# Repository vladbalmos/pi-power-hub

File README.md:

# System requirements
* micropython
* ampy
* minicom (optional)

# Development
Build micropython:

    cd [mycropython-dir]
    make -C mpy-cross

    cd [mycropython-dir]/ports/rp2
    make -j4 BOARD=PICO_W submodules
    make -j4 BOARD=PICO_W clean
    make -j4 BOARD=PICO_W
    
Set wifi SSID & password:

    cp wifi_credentials.template src/wifi_credentials.py
    # edit src/wifi_credentials.py and add SSID & SSID password

Init:

    pip3 install -r requirements.txt
    ./setup.sh
    make build
    
Run:

    make run
    
Clean

    make clean
    
Upload

    make upload
    
Build

    make build

# Topics
* vb/devices/power/pihub/request
    - device subscribes for state change requests
* vb/devices/power/pihub/response
    - device publishes state changes
* vb/devices/request
    - device subscribes for registration requests
* vb/devices/response
    - device publishes device registration data

# Status LED meanings:
* red
    - board initializing
* blue
    - connecting to mqtt server
* green
    - connected to mqtt server
* yellow
    - lost connection to mqtt

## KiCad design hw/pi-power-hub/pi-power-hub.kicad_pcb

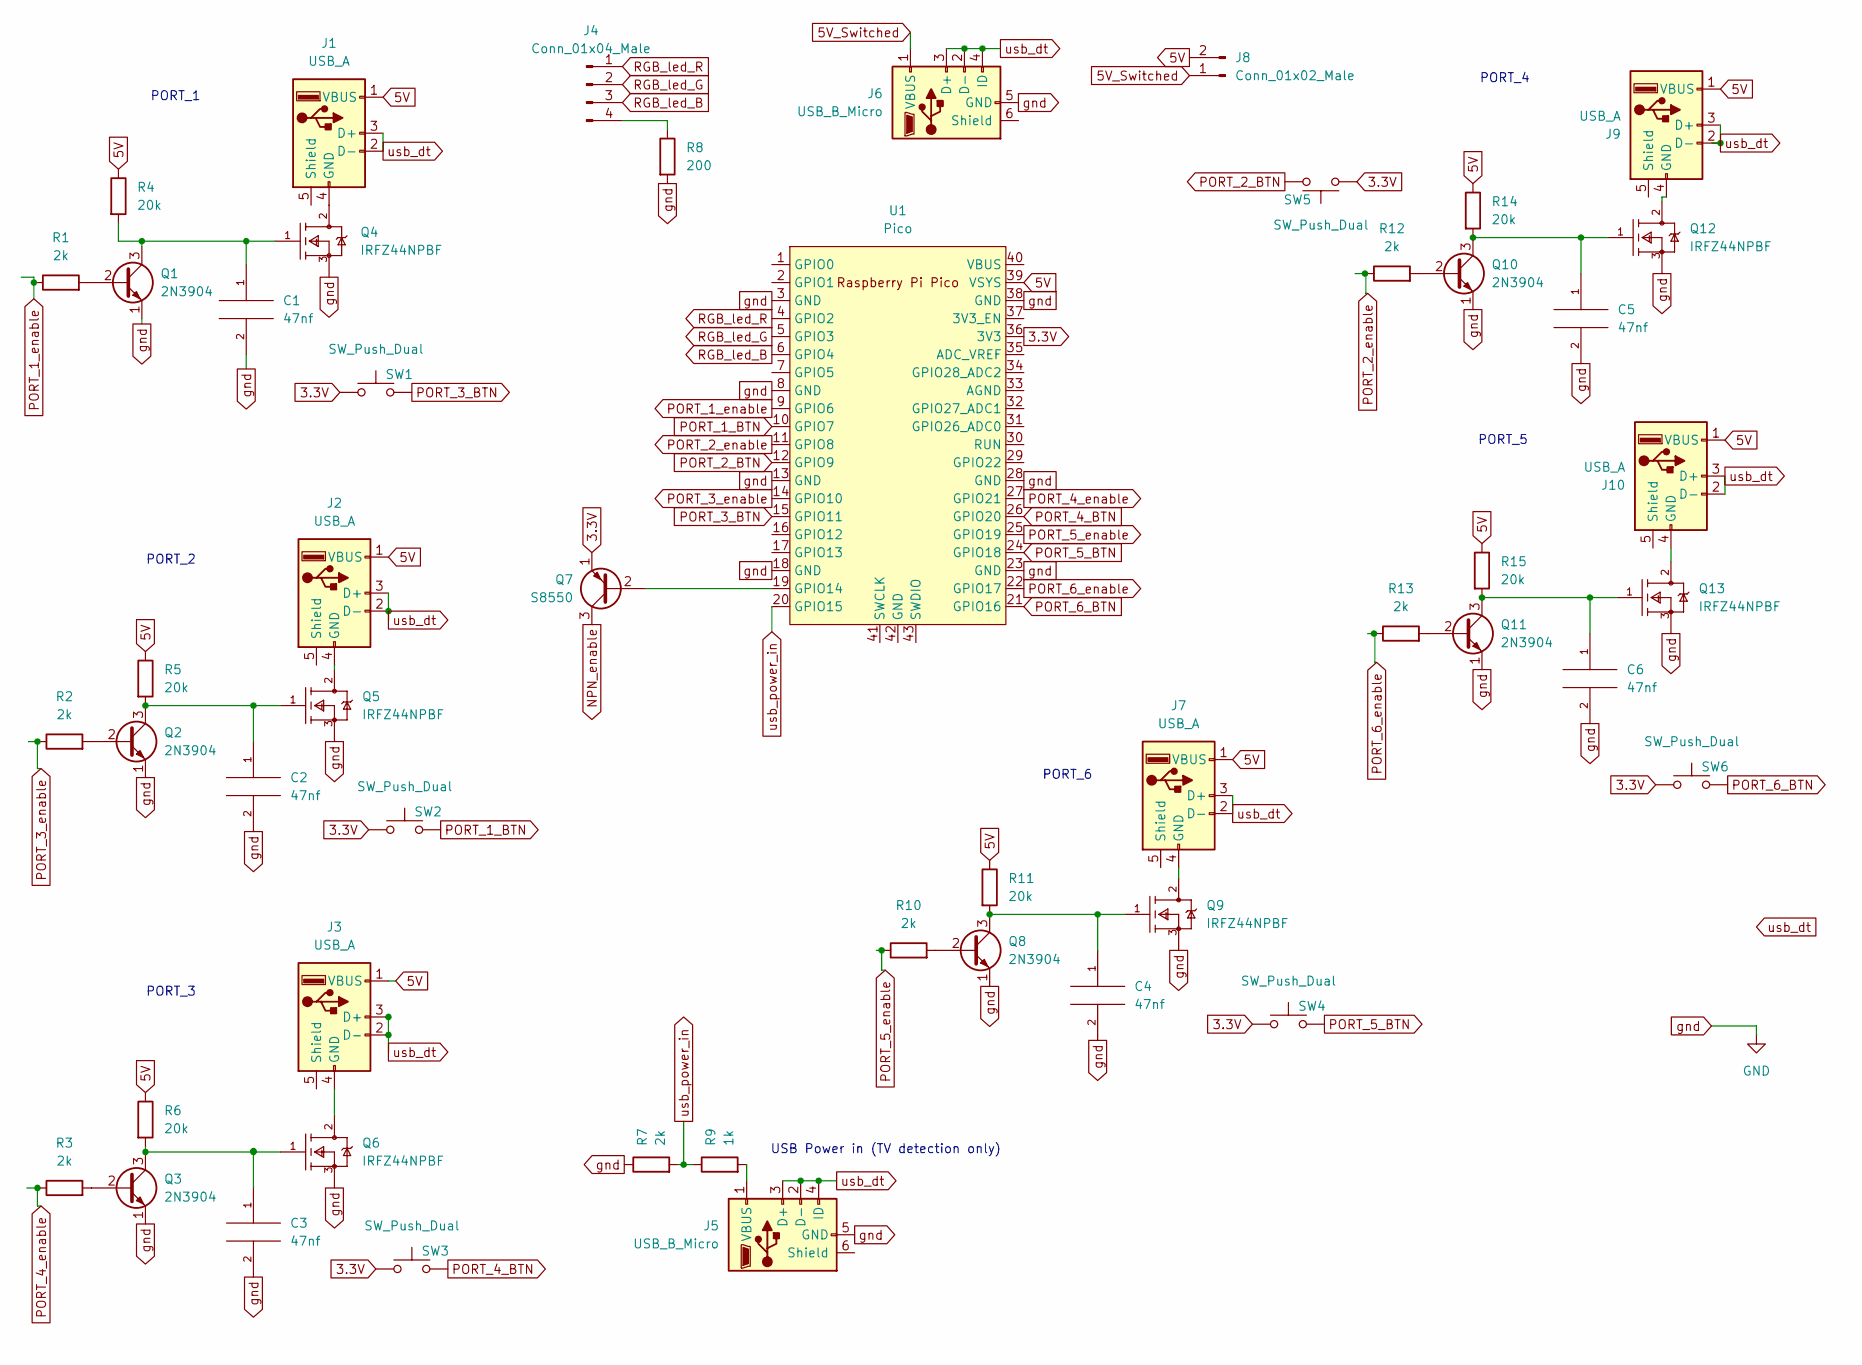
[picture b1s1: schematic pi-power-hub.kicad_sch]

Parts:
C1, C2, C3, C4, C5, C6: 47nf; C_Disc_D3.8mm_W2.6mm_P2.50mm
J1, J2, J3, J7, J9, J10: USB_A; USB_A_Molex_67643_Horizontal
J4: Conn_01x04_Male; JST_PH_B4B-PH-K_1x04_P2.00mm_Vertical
J5, J6: USB_B_Micro; USB_Micro-B_Amphenol_10103594-0001LF_Horizontal
J8: Conn_01x02_Male; JST_XH_B2B-XH-A_1x02_P2.50mm_Vertical
Q1, Q2, Q3, Q8, Q10, Q11: 2N3904; TO-92_Inline
Q4, Q5, Q6, Q9, Q12, Q13: IRFZ44NPBF; Infineon_Technologies_AG-IRFZ44NPBF-0; mouser part number 942-IRFZ44NPBF; digikey description N-Channel 55V 49A (Tc) 94W (Tc) Through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
Q7: S8550; TO-92_Inline
R1, R2, R3, R7, R10, R12, R13: 2k; R_Axial_DIN0207_L6.3mm_D2.5mm_P7.62mm_Horizontal
R4, R5, R6, R11, R14, R15: 20k; R_Axial_DIN0207_L6.3mm_D2.5mm_P7.62mm_Horizontal
R8: 200; R_Axial_DIN0207_L6.3mm_D2.5mm_P7.62mm_Horizontal
R9: 1k; R_Axial_DIN0207_L6.3mm_D2.5mm_P7.62mm_Horizontal
SW1, SW2, SW3, SW4, SW5, SW6: SW_Push_Dual; SW_PUSH_6mm_H8.5mm
U1: Pico; RPi_Pico_SMD_TH

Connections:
3.3V: Q7.1 (E), SW1.1, SW2.1, SW3.1, SW4.1, SW5.1, SW6.1, U1.36 (3V3)
5V: J1.1 (VBUS), J2.1 (VBUS), J3.1 (VBUS), J7.1 (VBUS), J8.2, J9.1 (VBUS), J10.1 (VBUS), R4.1, R5.1, R6.1, R11.1, R14.1, R15.1, U1.39 (VSYS); also elsewhere on the board
5V_Switched: J6.1 (VBUS), J8.1
NPN_enable: Q7.3 (C)
unnamed: C1.1, Q1.3 (C), Q4.1 (GATE), R4.2
unnamed: C2.1, Q2.3 (C), Q5.1 (GATE), R5.2
unnamed: C3.1, Q3.3 (C), Q6.1 (GATE), R6.2
unnamed: C4.1, Q8.3 (C), Q9.1 (GATE), R11.2
unnamed: C5.1, Q10.3 (C), Q12.1 (GATE), R14.2
unnamed: C6.1, Q11.3 (C), Q13.1 (GATE), R15.2
unnamed: J1.4 (GND), Q4.2 (DRAIN)
unnamed: J2.4 (GND), Q5.2 (DRAIN)
unnamed: J3.4 (GND), Q6.2 (DRAIN)
unnamed: J4.4, R8.1
unnamed: J5.1 (VBUS), R9.2
unnamed: J7.4 (GND), Q9.2 (DRAIN)
unnamed: J9.4 (GND), Q12.2 (DRAIN)
unnamed: J10.4 (GND), Q13.2 (DRAIN)
unnamed: Q1.2 (B), R1.2
unnamed: Q2.2 (B), R2.2
unnamed: Q3.2 (B), R3.2
unnamed: Q7.2 (B), U1.19 (GPIO14)
unnamed: Q8.2 (B), R10.2
unnamed: Q10.2 (B), R12.2
unnamed: Q11.2 (B), R13.2
PORT_1_BTN: SW2.2, U1.10 (GPIO7)
PORT_1_enable: R1.1, U1.9 (GPIO6)
PORT_2_BTN: SW5.2, U1.12 (GPIO9)
PORT_2_enable: R12.1, U1.11 (GPIO8)
PORT_3_BTN: SW1.2, U1.15 (GPIO11)
PORT_3_enable: R2.1, U1.14 (GPIO10)
PORT_4_BTN: SW3.2, U1.26 (GPIO20)
PORT_4_enable: R3.1, U1.27 (GPIO21)
PORT_5_BTN: SW4.2, U1.24 (GPIO18)
PORT_5_enable: R10.1, U1.25 (GPIO19)
PORT_6_BTN: SW6.2, U1.21 (GPIO16)
PORT_6_enable: R13.1, U1.22 (GPIO17)
RGB_led_B: J4.3, U1.6 (GPIO4)
RGB_led_G: J4.2, U1.5 (GPIO3)
RGB_led_R: J4.1, U1.4 (GPIO2)
gnd: C1.2, C2.2, C3.2, C4.2, C5.2, C6.2, J5.5 (GND), J6.5 (GND), Q1.1 (E), Q2.1 (E), Q3.1 (E), Q4.3 (SOURCE), Q5.3 (SOURCE), Q6.3 (SOURCE), Q8.1 (E), Q9.3 (SOURCE), Q10.1 (E), Q11.1 (E), Q12.3 (SOURCE), Q13.3 (SOURCE), R7.1, R8.2, U1.3 (GND), U1.8 (GND), U1.13 (GND), U1.18 (GND), U1.23 (GND), U1.28 (GND), U1.38 (GND)
usb_dt: J1.2 (D-), J1.3 (D+), J2.2 (D-), J2.3 (D+), J3.2 (D-), J3.3 (D+), J5.2 (D-), J5.3 (D+), J5.4 (ID), J6.2 (D-), J6.3 (D+), J6.4 (ID), J7.2 (D-), J7.3 (D+), J9.2 (D-), J9.3 (D+), J10.2 (D-), J10.3 (D+)
usb_power_in: R7.2, R9.1, U1.20 (GPIO15)

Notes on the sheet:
PORT_2
PORT_3
PORT_5
USB Power in (TV detection only)
PORT_4
PORT_1
PORT_6

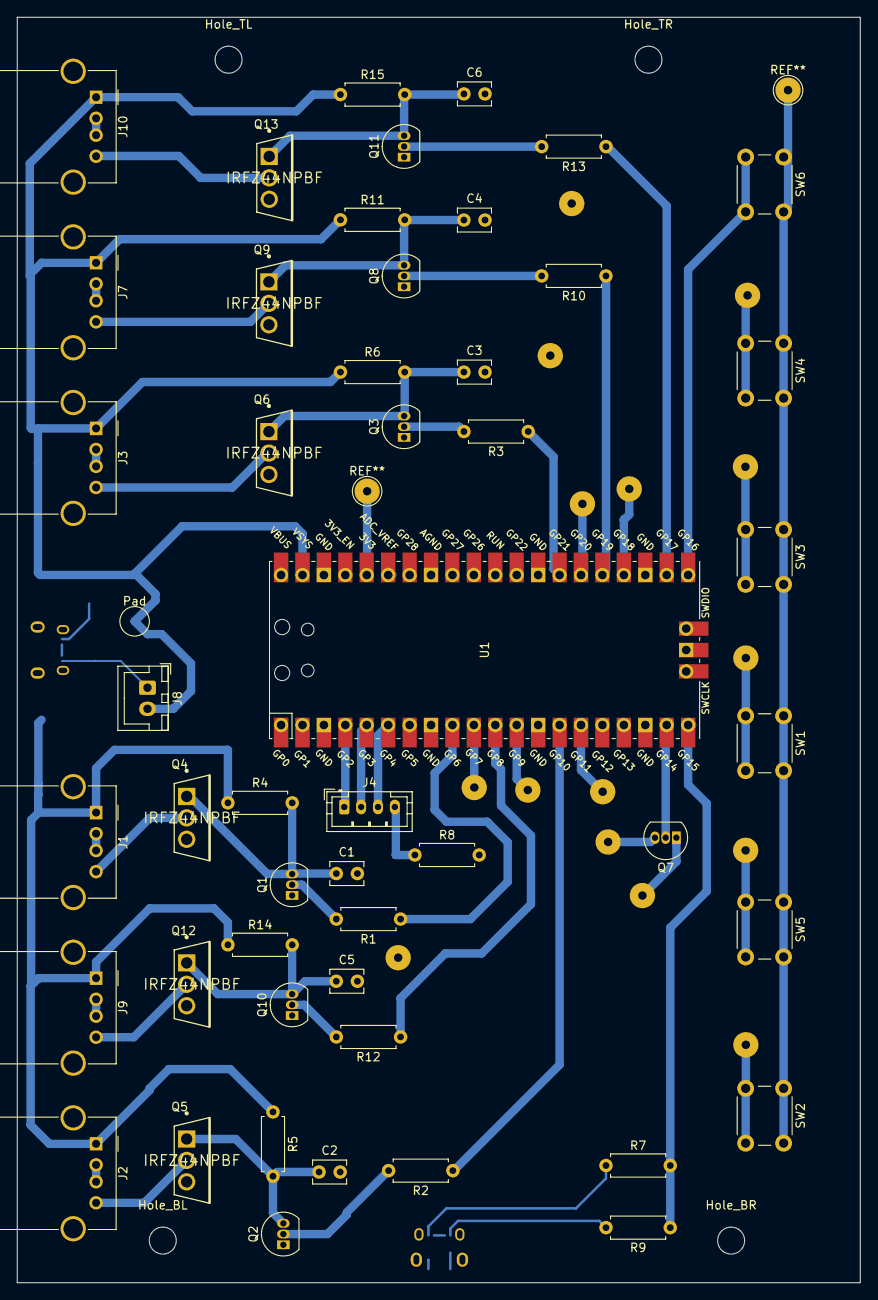
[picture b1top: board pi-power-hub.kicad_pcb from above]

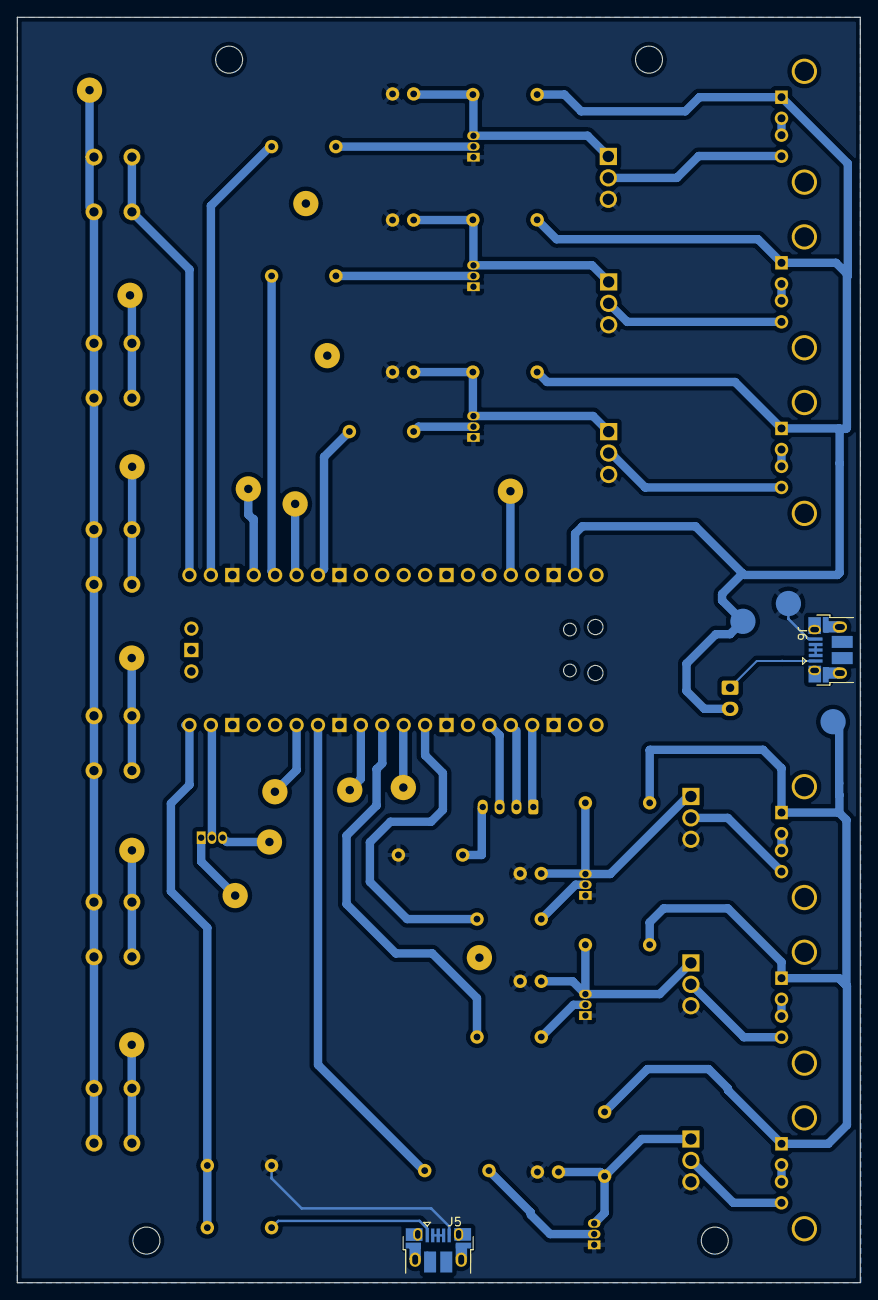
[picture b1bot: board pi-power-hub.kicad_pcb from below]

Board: 2 copper layers, 99.9 x 150.0 mm, 56 parts (2 on the bottom side), 42 nets.

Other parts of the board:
Hole_BL: MountingHole_3.2mm_M3
Hole_BR: MountingHole_3.2mm_M3
Hole_TL: MountingHole_3.2mm_M3
Hole_TR: MountingHole_3.2mm_M3
Pad: TestPoint_Pad_D3.0mm

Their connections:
5V: Pad.1; also elsewhere on the board

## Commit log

2023-01-21 Squashed 'lib/micropython-async/' content from commit 076f019
    git-subtree-dir: lib/micropython-async
    git-subtree-split: 076f0195dc5896a5f95ec1f110d885e94481664a
2023-01-25 Update devices features schema
2023-01-28 Refactor features schema
2023-02-01 Implement networking via mqtt
2023-02-08 Bug fix
2023-02-08 Remove extra debug statement
2023-02-11 Add status RGB led
2023-02-11 Fine tune RGB status led
2023-02-11 Add lTSpice simulation
2023-02-11 Fine tuning
2023-02-19 Change output pins order
2023-02-19 Change mqtt server address
2023-02-19 Improve readme and add board pics
2023-02-24 Add 3d model and slicer file
2023-02-24 Update 3d model
2023-03-03 Update 3d print settings
2023-03-05 Update models
2023-04-10 Add requirements.txt
2024-07-14 Bug fixes
2024-07-14 Fix dependencies
